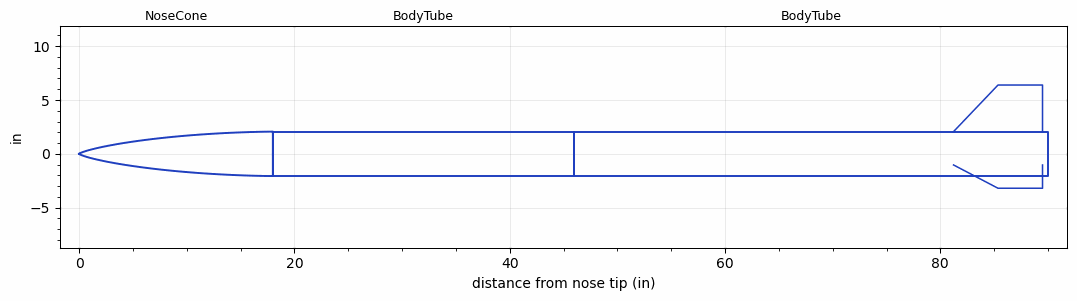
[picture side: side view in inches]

<RASAeroDocument>
 <FileVersion>2</FileVersion>
 <RocketDesign>
  <NoseCone>
   <Length>17.9921</Length>
   <Diameter>4.125</Diameter>
   <Shape>LV-Haack</Shape>
   <Location>0</Location>
  </NoseCone>
  <BodyTube>
   <Length>28</Length>
   <Diameter>4.125</Diameter>
   <Location>17.9921</Location>
  </BodyTube>
  <BodyTube>
   <Length>44</Length>
   <Diameter>4.125</Diameter>
   <Location>45.9921</Location>
   <Fin>
    <Count>3</Count>
    <Chord>8.2677</Chord>
    <Span>4.3307</Span>
    <SweepDistance>4.1338</SweepDistance>
    <TipChord>4.1338</TipChord>
    <Thickness>0.25</Thickness>
    <Location>8.7677</Location>
    <AirfoilSection>Single Wedge</AirfoilSection>
   </Fin>
  </BodyTube>
  <Surface>Smooth (Zero Roughness)</Surface>
  <ModifiedBarrowman>True</ModifiedBarrowman>
  <Turbulence>False</Turbulence>
  <UseBooster1>False</UseBooster1>
  <UseBooster2>False</UseBooster2>
 </RocketDesign>
 <LaunchSite>
  <Altitude>0</Altitude>
  <Pressure>0</Pressure>
  <RodAngle>6</RodAngle>
  <RodLength>2.2</RodLength>
  <Temperature>74</Temperature>
  <WindSpeed>33</WindSpeed>
 </LaunchSite>
 <Recovery>
  <Altitude1>1000</Altitude1>
  <Altitude2>1000</Altitude2>
  <DeviceType1>Parachute</DeviceType1>
  <DeviceType2>Parachute</DeviceType2>
  <Event1>True</Event1>
  <Event2>True</Event2>
  <Size1>12</Size1>
  <Size2>48</Size2>
  <EventType1>Apogee</EventType1>
  <EventType2>Apogee</EventType2>
  <CD1>0.97</CD1>
  <CD2>2.2</CD2>
 </Recovery>
 <SimulationList>
  <Simulation>
   <SustainerEngine>K570  (CTI)</SustainerEngine>
   <SustainerLaunchWt>14.04</SustainerLaunchWt>
   <SustainerNozzleDiameter>2.27</SustainerNozzleDiameter>
   <SustainerCG>60</SustainerCG>
   <SustainerIgnitionDelay>0</SustainerIgnitionDelay>
   <Booster1SeparationDelay>0</Booster1SeparationDelay>
   <Booster1IgnitionDelay>0</Booster1IgnitionDelay>
   <IncludeBooster1>False</IncludeBooster1>
   <Booster2Delay>0</Booster2Delay>
   <IncludeBooster2>False</IncludeBooster2>
   <TimetoApogee>19.46035</TimetoApogee>
   <MaxAltitude>7083.411</MaxAltitude>
   <MaxVelocity>917.3298</MaxVelocity>
   <OptimumWt>10.53</OptimumWt>
   <OptimumMaxAlt>10.53</OptimumMaxAlt>
  </Simulation>
 </SimulationList>
</RASAeroDocument>
